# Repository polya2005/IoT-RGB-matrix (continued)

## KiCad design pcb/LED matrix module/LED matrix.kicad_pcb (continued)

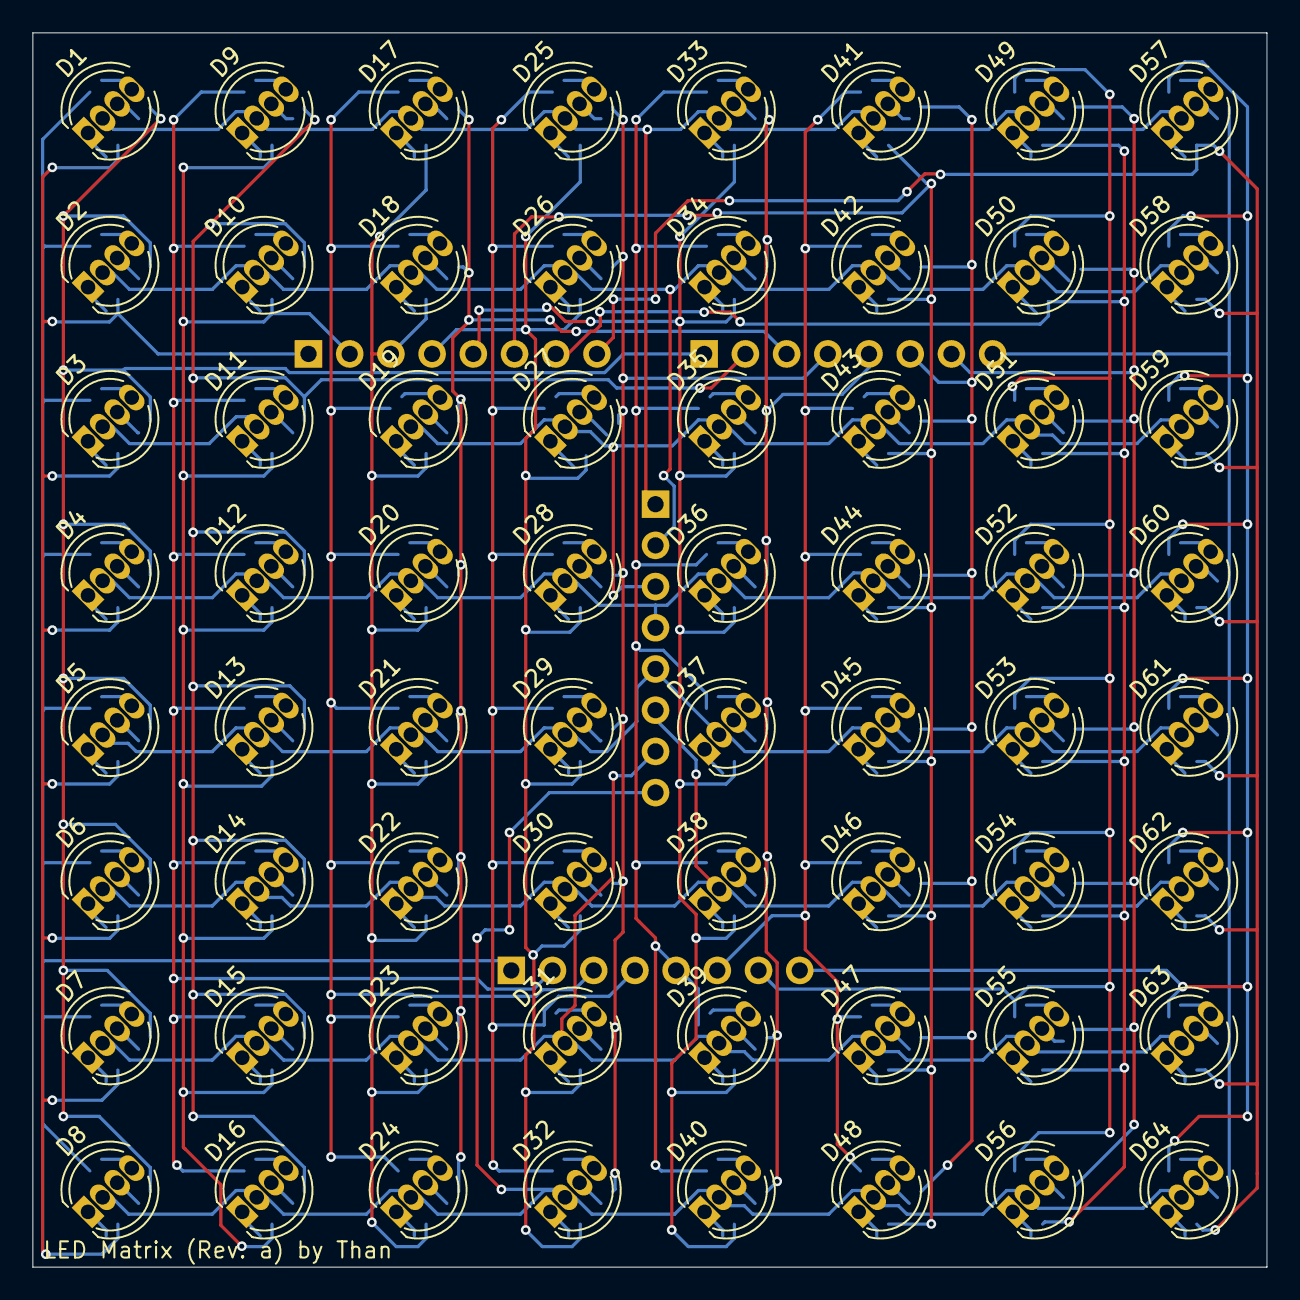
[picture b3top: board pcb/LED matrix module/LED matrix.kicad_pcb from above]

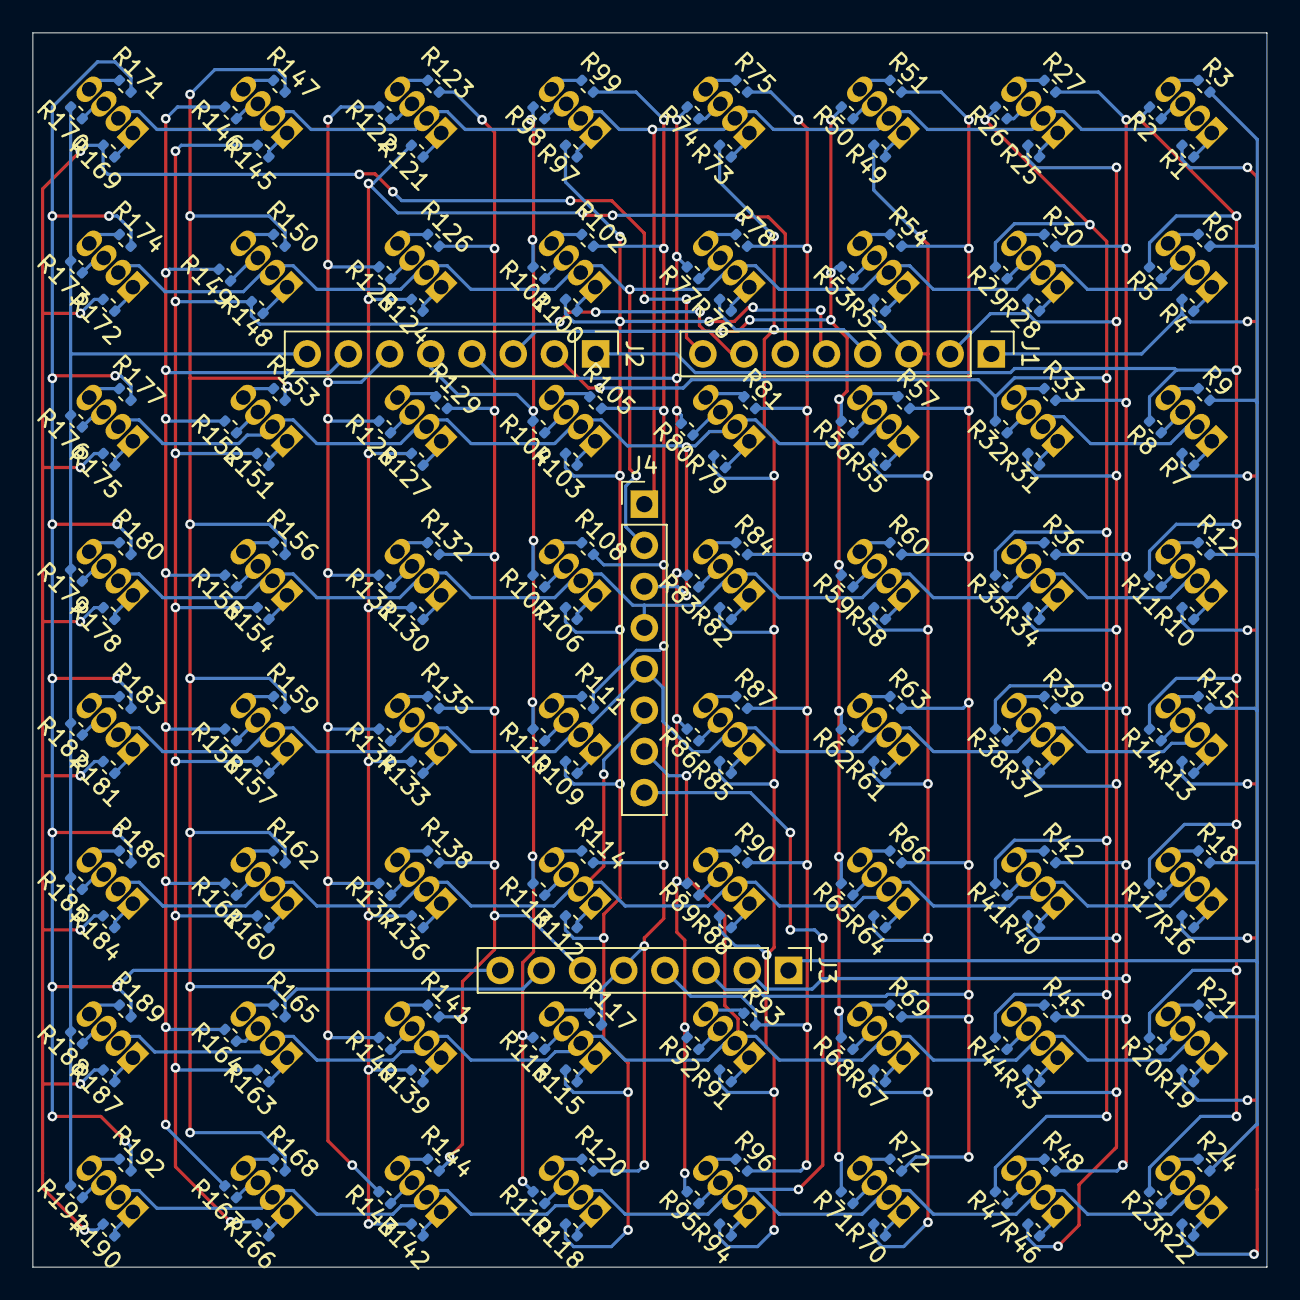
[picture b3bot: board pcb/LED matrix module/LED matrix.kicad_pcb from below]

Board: 2 copper layers, 76.1 x 76.1 mm, 260 parts (196 on the bottom side), 224 nets.

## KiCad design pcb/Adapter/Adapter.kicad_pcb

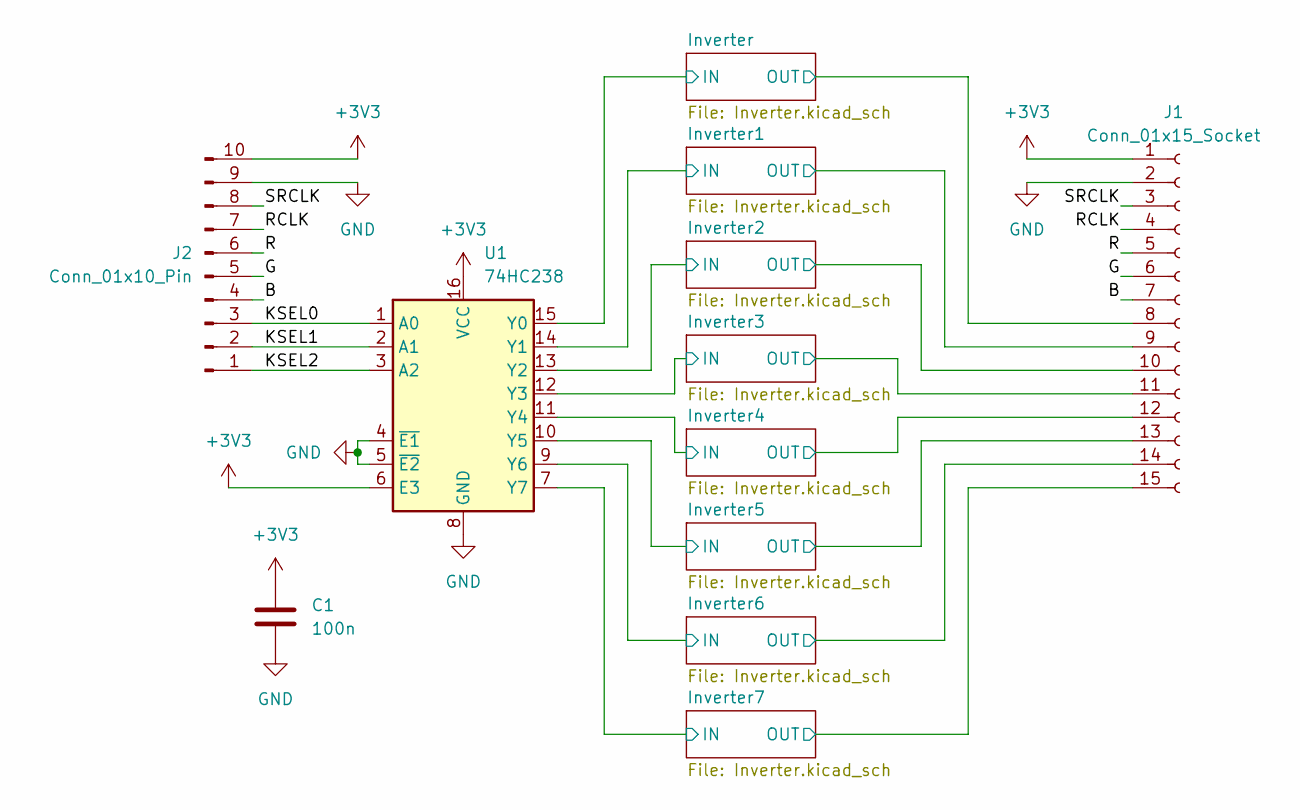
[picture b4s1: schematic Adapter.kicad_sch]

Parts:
C1: 100n; C_1206_3216Metric_Pad1.33x1.80mm_HandSolder
J1: Conn_01x15_Socket; PinSocket_1x15_P2.54mm_Horizontal
J2: Conn_01x10_Pin; PinHeader_1x10_P2.54mm_Horizontal
U1: 74HC238; TSSOP-16_4.4x5mm_P0.65mm

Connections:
+3V3: C1.1, J1.1, J2.10, U1.6 (E3), U1.16 (VCC)
/B: J1.7, J2.4
/G: J1.6, J2.5
/Inverter1/IN: U1.14 (Y1); also elsewhere on the board
/Inverter1/OUT: J1.9; also elsewhere on the board
/Inverter2/IN: U1.13 (Y2); also elsewhere on the board
/Inverter2/OUT: J1.10; also elsewhere on the board
/Inverter3/IN: U1.12 (Y3); also elsewhere on the board
/Inverter3/OUT: J1.11; also elsewhere on the board
/Inverter4/IN: U1.11 (Y4); also elsewhere on the board
/Inverter4/OUT: J1.12; also elsewhere on the board
/Inverter5/IN: U1.10 (Y5); also elsewhere on the board
/Inverter5/OUT: J1.13; also elsewhere on the board
/Inverter6/IN: U1.9 (Y6); also elsewhere on the board
/Inverter6/OUT: J1.14; also elsewhere on the board
/Inverter7/IN: U1.7 (Y7); also elsewhere on the board
/Inverter7/OUT: J1.15; also elsewhere on the board
/Inverter/IN: U1.15 (Y0); also elsewhere on the board
/Inverter/OUT: J1.8; also elsewhere on the board
/KSEL0: J2.3, U1.1 (A0)
/KSEL1: J2.2, U1.2 (A1)
/KSEL2: J2.1, U1.3 (A2)
/R: J1.5, J2.6
/RCLK: J1.4, J2.7
/SRCLK: J1.3, J2.8
GND: C1.2, J1.2, J2.9, U1.4 (~E1), U1.5 (~E2), U1.8 (GND); also elsewhere on the board

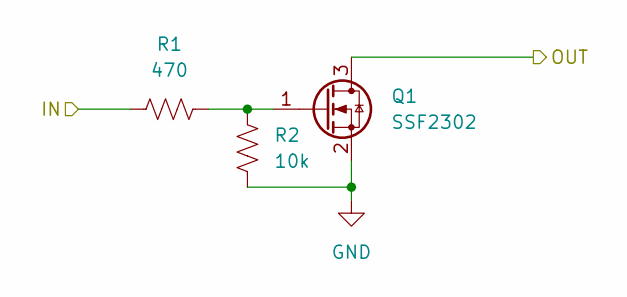
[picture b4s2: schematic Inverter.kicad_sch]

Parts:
Q1: SSF2302; SOT-23_Handsoldering
R1: 470; R_0805_2012Metric_Pad1.20x1.40mm_HandSolder
R2: 10k; R_0805_2012Metric_Pad1.20x1.40mm_HandSolder

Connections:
/Inverter/IN: R1.1; also elsewhere on the board
/Inverter/OUT: Q1.3 (D); also elsewhere on the board
GND: Q1.2 (S), R2.2; also elsewhere on the board
unnamed: Q1.1 (G), R1.2, R2.1

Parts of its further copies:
Q2, Q3, Q4, Q5, Q6, Q7, Q8: SSF2302; SOT-23_Handsoldering
R3, R5, R7, R9, R11, R13, R15: 470; R_0805_2012Metric_Pad1.20x1.40mm_HandSolder
R4, R6, R8, R10, R12, R14, R16: 10k; R_0805_2012Metric_Pad1.20x1.40mm_HandSolder

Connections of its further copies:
/Inverter1/IN: R3.1; also elsewhere on the board
/Inverter1/OUT: Q2.3 (D); also elsewhere on the board
/Inverter2/IN: R5.1; also elsewhere on the board
/Inverter2/OUT: Q3.3 (D); also elsewhere on the board
/Inverter3/IN: R7.1; also elsewhere on the board
/Inverter3/OUT: Q4.3 (D); also elsewhere on the board
/Inverter4/IN: R9.1; also elsewhere on the board
/Inverter4/OUT: Q5.3 (D); also elsewhere on the board
/Inverter5/IN: R11.1; also elsewhere on the board
/Inverter5/OUT: Q6.3 (D); also elsewhere on the board
/Inverter6/IN: R13.1; also elsewhere on the board
/Inverter6/OUT: Q7.3 (D); also elsewhere on the board
/Inverter7/IN: R15.1; also elsewhere on the board
/Inverter7/OUT: Q8.3 (D); also elsewhere on the board
GND: Q2.2 (S), Q3.2 (S), Q4.2 (S), Q5.2 (S), Q6.2 (S), Q7.2 (S), Q8.2 (S), R4.2, R6.2, R8.2, R10.2, R12.2, R14.2, R16.2; also elsewhere on the board
unnamed: Q2.1 (G), R3.2, R4.1
unnamed: Q3.1 (G), R5.2, R6.1
unnamed: Q4.1 (G), R7.2, R8.1
unnamed: Q5.1 (G), R9.2, R10.1
unnamed: Q6.1 (G), R11.2, R12.1
unnamed: Q7.1 (G), R13.2, R14.1
unnamed: Q8.1 (G), R15.2, R16.1

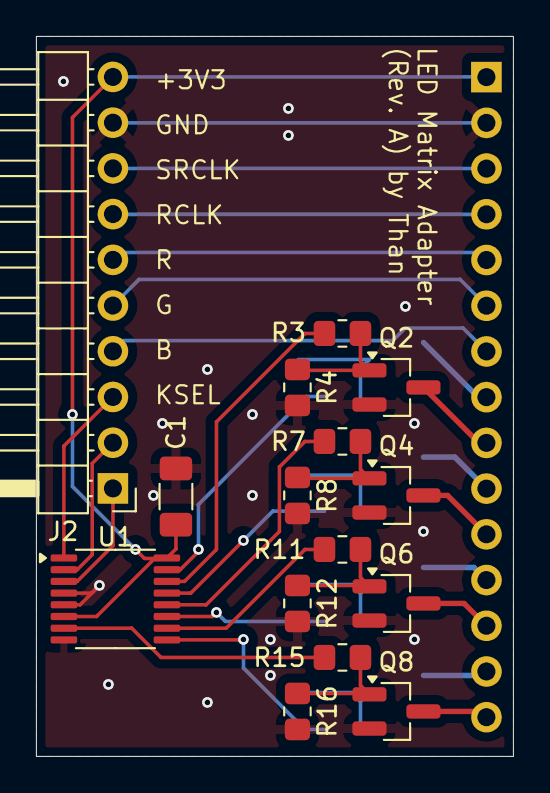
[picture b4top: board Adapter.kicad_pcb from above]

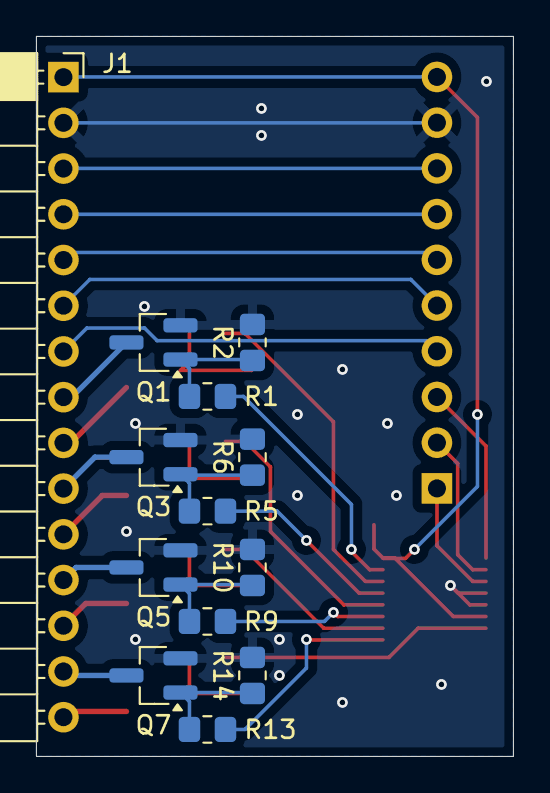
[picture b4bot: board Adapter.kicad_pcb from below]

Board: 2 copper layers, 26.5 x 40.0 mm, 28 parts (13 on the bottom side), 34 nets.

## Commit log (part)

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2025-12-21 Change to legal name
2025-12-21 first readme draft
2025-12-21 Add gitignore
2025-12-26 Initial PCB commit
2025-12-26 export step file for adapter pcb
2025-12-26 export carrier pcb step model
2025-12-26 export matrix module step model
2026-01-01 fix wrong footprint/symbol
2026-01-02 Create PIO project
2026-01-07 move matrix serial pin definitions
2026-01-17 refactor serial pin defns
2026-01-17 ignore .DS_Store
2026-01-20 configure for test
2026-01-23 Migrate to espidf
2026-03-02 add asm matrix impl and modify c impl
2026-03-02 combine redundant lines
